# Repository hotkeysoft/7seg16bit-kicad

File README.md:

# Six-digit seven-segment indicator for 16 bit values
Rev A August 2019

- ATmega8535 microcontroller running at 8MHz (internal clock)
- 3x2 digit 7-segment display
- Configurable modes via jumpers:
  - Decimal / HEX mode
    - Signed Decimal (-32768-32767)
    - Unsigned Decimal (0-65535)
    - Hexadecimal (0-FFFF)
  - Latch mode
    - Latch value on L->H transition
    - Latch value on H->L transition
    - Unlatched (live display)

Images
============
|Front                                                 | Back                                              |
|------------------------------------------------------|---------------------------------------------------|
|||

### Schematics (pdf)
- [Complete schematics](./img/schema.pdf)

### PCB Images (svg)
- [Top](./img/pcb-front.svg)
- [Bottom](./img/pcb-back.svg)

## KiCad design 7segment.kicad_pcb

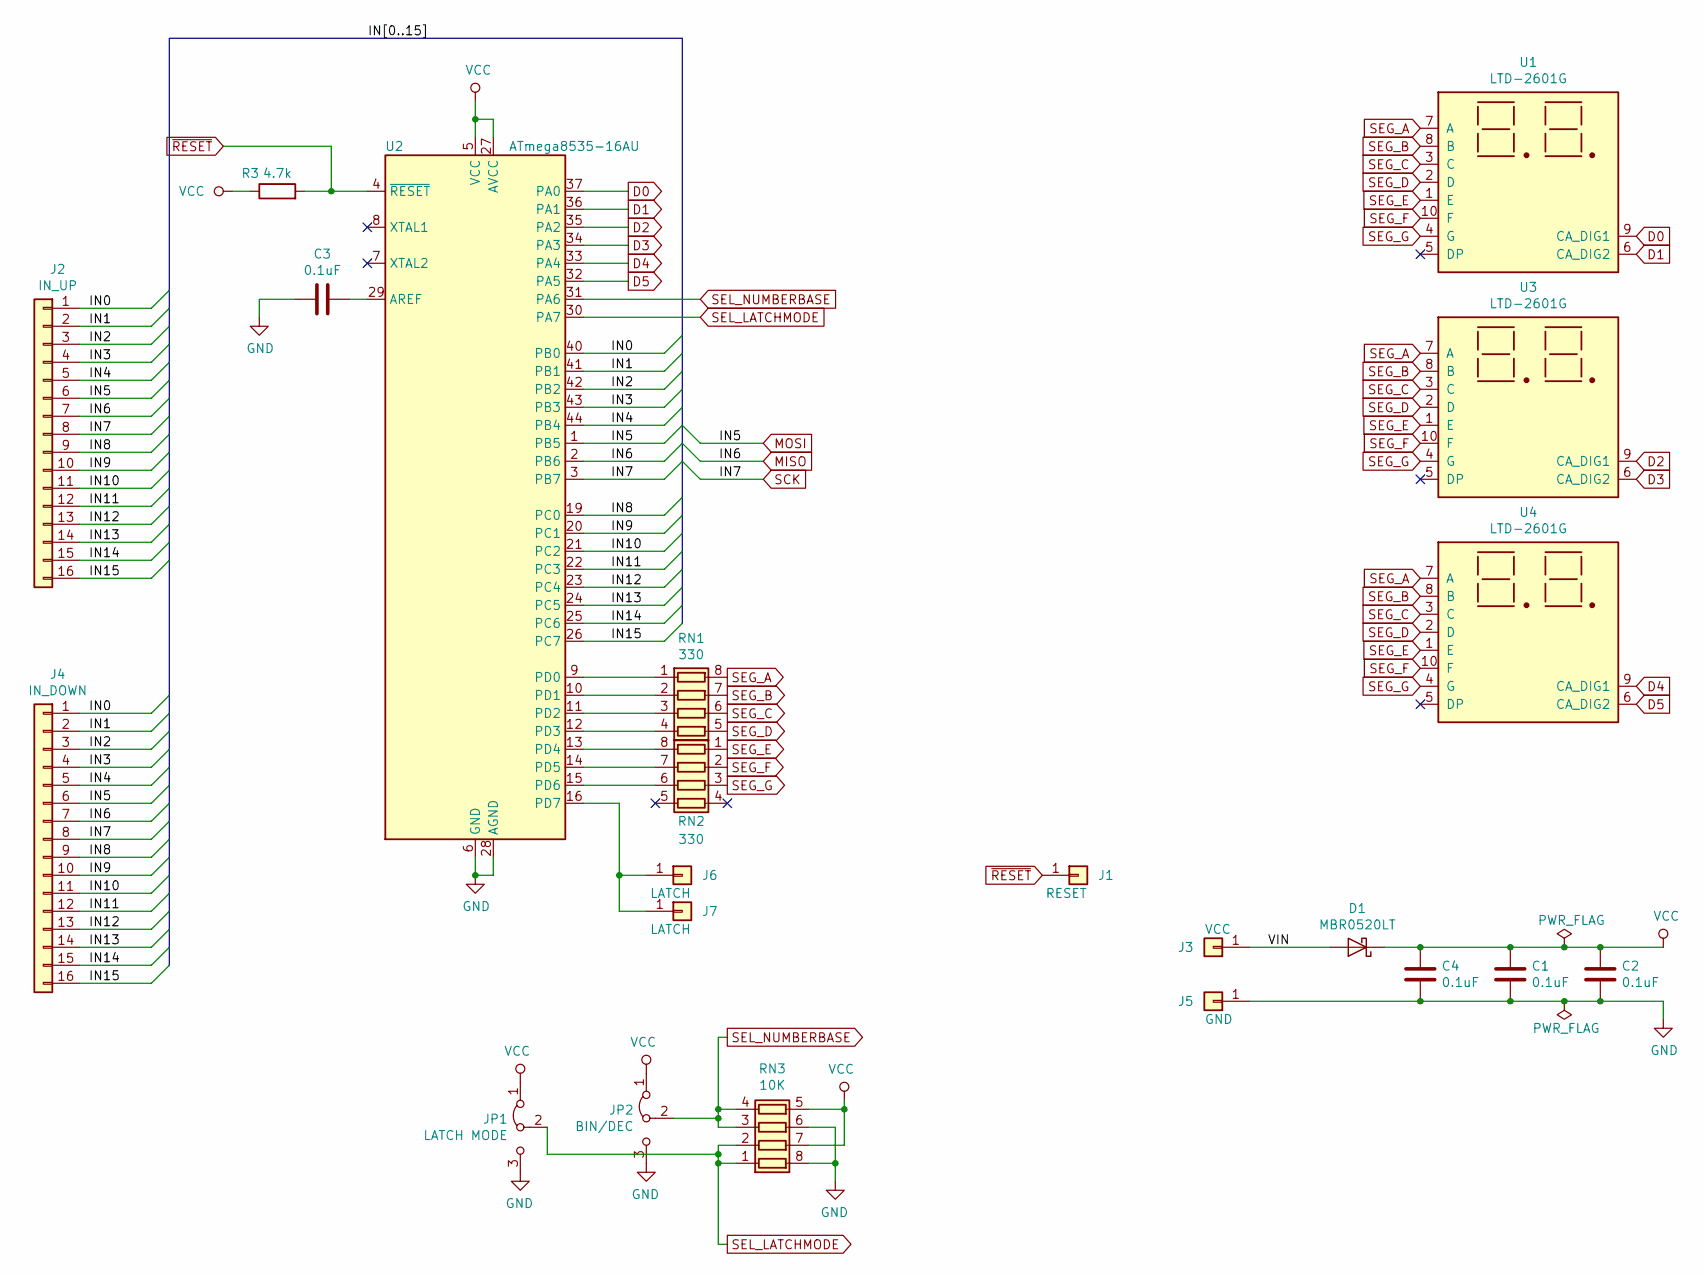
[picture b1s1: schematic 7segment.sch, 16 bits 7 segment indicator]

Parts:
C1, C2, C3, C4: 0.1uF; C_0805_2012Metric_Pad1.15x1.40mm_HandSolder
D1: MBR0520LT; D_SOD-123
J1: RESET; PinHeader_1x01_P2.54mm_Vertical
J2: IN_UP; PinHeader_1x16_P2.54mm_Vertical
J3: VCC; PinHeader_1x01_P2.54mm_Vertical
J4: IN_DOWN; PinHeader_1x16_P2.54mm_Vertical
J5: GND; PinHeader_1x01_P2.54mm_Vertical
J6, J7: LATCH; PinHeader_1x01_P2.54mm_Vertical
JP1: LATCH MODE; PinHeader_1x03_P2.54mm_Vertical
JP2: BIN/DEC; PinHeader_1x03_P2.54mm_Vertical
R3: 4.7k; R_0805_2012Metric_Pad1.15x1.40mm_HandSolder
RN1, RN2: 330; R_Array_Convex_4x0603
RN3: 10K; R_Array_Convex_4x0603
U1, U3, U4: LTD-2601G
U2: ATmega8535-16AU; TQFP-44_10x10mm_P0.8mm

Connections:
/IN0: J2.1, J4.1, U2.40 (PB0)
/IN1: J2.2, J4.2, U2.41 (PB1)
/IN2: J2.3, J4.3, U2.42 (PB2)
/IN3: J2.4, J4.4, U2.43 (PB3)
/IN4: J2.5, J4.5, U2.44 (PB4)
/IN8: J2.9, J4.9, U2.19 (PC0)
/IN9: J2.10, J4.10, U2.20 (PC1)
/IN10: J2.11, J4.11, U2.21 (PC2)
/IN11: J2.12, J4.12, U2.22 (PC3)
/IN12: J2.13, J4.13, U2.23 (PC4)
/IN13: J2.14, J4.14, U2.24 (PC5)
/IN14: J2.15, J4.15, U2.25 (PC6)
/IN15: J2.16, J4.16, U2.26 (PC7)
/VIN: D1.2 (A), J3.1
D0: U1.9 (CA_DIG1), U2.37 (PA0)
D1: U1.6 (CA_DIG2), U2.36 (PA1)
D2: U2.35 (PA2), U3.9 (CA_DIG1)
D3: U2.34 (PA3), U3.6 (CA_DIG2)
D4: U2.33 (PA4), U4.9 (CA_DIG1)
D5: U2.32 (PA5), U4.6 (CA_DIG2)
GND: C1.2, C2.2, C3.1, C4.2, J5.1, JP1.3 (B), JP2.3 (B), RN3.6 (R3.2), RN3.8 (R1.2), U2.6 (GND), U2.18 (GND), U2.28 (AGND), U2.39 (GND)
MISO: J2.7, J4.7, U2.2 (PB6)
MOSI: J2.6, J4.6, U2.1 (PB5)
unnamed: C3.2, U2.29 (AREF)
unnamed: J6.1, J7.1, U2.16 (PD7)
unnamed: RN1.1 (R1.1), U2.9 (PD0)
unnamed: RN1.2 (R2.1), U2.10 (PD1)
unnamed: RN1.3 (R3.1), U2.11 (PD2)
unnamed: RN1.4 (R4.1), U2.12 (PD3)
unnamed: RN2.6 (R3.2), U2.15 (PD6)
unnamed: RN2.7 (R2.2), U2.14 (PD5)
unnamed: RN2.8 (R1.2), U2.13 (PD4)
SCK: J2.8, J4.8, U2.3 (PB7)
SEG_A: RN1.8 (R1.2), U1.7 (A), U3.7 (A), U4.7 (A)
SEG_B: RN1.7 (R2.2), U1.8 (B), U3.8 (B), U4.8 (B)
SEG_C: RN1.6 (R3.2), U1.3 (C), U3.3 (C), U4.3 (C)
SEG_D: RN1.5 (R4.2), U1.2 (D), U3.2 (D), U4.2 (D)
SEG_E: RN2.1 (R1.1), U1.1 (E), U3.1 (E), U4.1 (E)
SEG_F: RN2.2 (R2.1), U1.10 (F), U3.10 (F), U4.10 (F)
SEG_G: RN2.3 (R3.1), U1.4 (G), U3.4 (G), U4.4 (G)
SEL_LATCHMODE: JP1.2 (C), RN3.1 (R1.1), RN3.2 (R2.1), U2.30 (PA7)
SEL_NUMBERBASE: JP2.2 (C), RN3.3 (R3.1), RN3.4 (R4.1), U2.31 (PA6)
VCC: C1.1, C2.1, C4.1, D1.1 (K), JP1.1 (A), JP2.1 (A), R3.1, RN3.5 (R4.2), RN3.7 (R2.2), U2.5 (VCC), U2.17 (VCC), U2.27 (AVCC), U2.38 (VCC)
~RESET: J1.1, R3.2, U2.4 (~RESET)

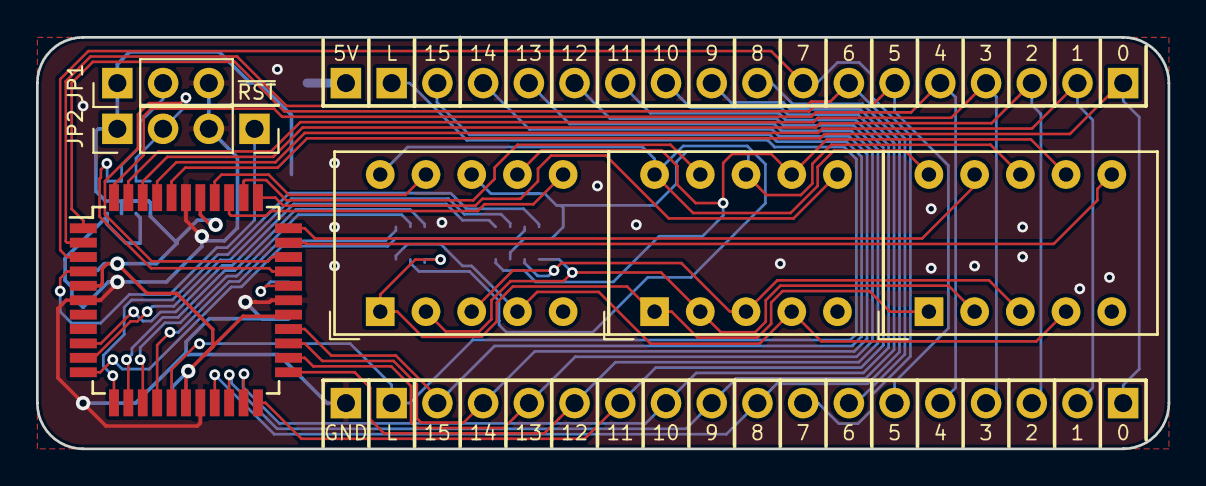
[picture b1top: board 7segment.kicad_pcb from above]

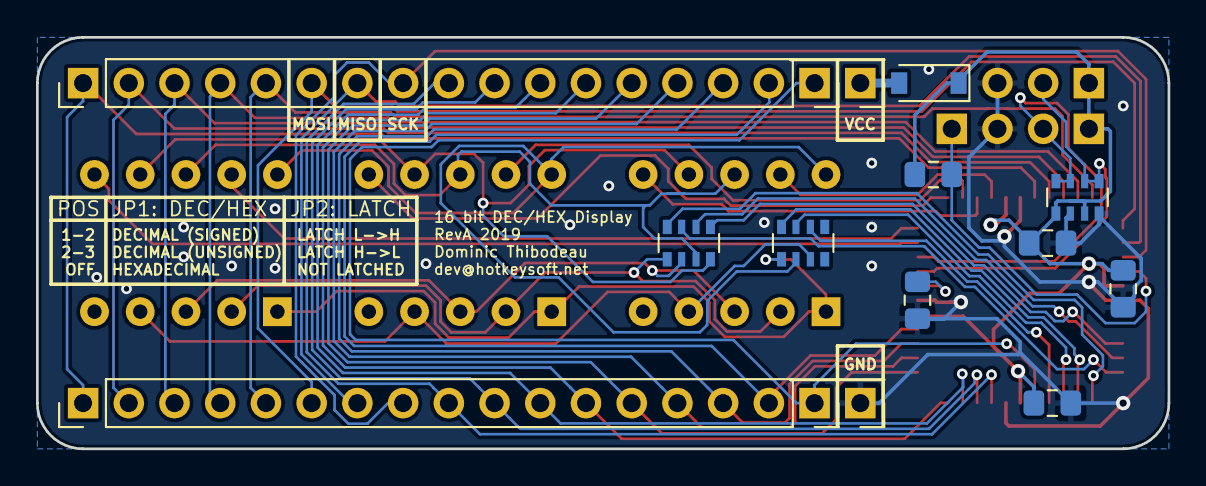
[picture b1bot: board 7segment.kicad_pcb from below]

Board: 2 copper layers, 62.9 x 22.9 mm, 22 parts (15 on the bottom side), 44 nets.

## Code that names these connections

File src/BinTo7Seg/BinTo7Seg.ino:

/* Binary to 7 Segment display (16 bits)
 * Rev A 
 * 2019-08-19 Dominic Thibodeau
 * 
 * Modes: Hex / Signed Decimal / Unsigned Decimal
 *        Latched / Live
 *        
 * Target: ATmega8535
 */

/*
 * IN0-IN7:  PB0-PB7
 * IN8-IN15: PC0-PC7
 * 
 * D0: PA0
 * D1: PA1
 * D2: PA2
 * D3: PA3
 * D4: PA4
 * D5: PA5
 * 
 * IN_LATCH: PD7
 * 
 * SEGA-SEGG: PD0-PD6
 * 
 * SEL_NUMBERBASE: PA6
 * SEL_LATCHMODE: PA7
 */

#define PA 0
#define PB 1
#define PC 2
#define PD 3

#define SEL_D0 24
#define SEL_D1 25
#define SEL_D2 26
#define SEL_D3 27
#define SEL_D4 28
#define SEL_D5 29

#define SEL_NUMBERBASE A6
#define SEL_LATCHMODE A7

#define IN_LATCH 15

const int digitDelay = 2;

bool triggeredOnce = false;
int lastLatchPinState;
uint16_t latchedInput = 0;

enum DIGIT {
  DIGIT_D0 = SEL_D0,
  DIGIT_D1 = SEL_D1,
  DIGIT_D2 = SEL_D2,
  DIGIT_D3 = SEL_D3,
  DIGIT_D4 = SEL_D4,
  DIGIT_D5 = SEL_D5,
};

enum LATCHMODE {
  LATCH_LH,
  LATCH_HL,
  LATCH_LIVE
};

enum NUMBERBASE {
  NB_SIGNED_DEC,
  NB_UNSIGNED_DEC,
  NB_HEX
};

LATCHMODE getLatchMode() {
  int value = analogRead(SEL_LATCHMODE);
  if (value < 300)
    return LATCH_LH;
  else if (value > 700)
    return LATCH_HL;
  else 
    return LATCH_LIVE;  
}

NUMBERBASE getNumberBase() {
  int value = analogRead(SEL_NUMBERBASE);
  if (value < 300)
    return NB_SIGNED_DEC;
  else if (value > 700)
    return NB_UNSIGNED_DEC;
  else 
    return NB_HEX;      
}

uint16_t readInput() {
  return (portRead(PC) << 8) + portRead(PB);
}

void setup() {
  // Segments
  portMode(PD, OUTPUT);
  
  // Inputs
  portMode(PB, INPUT);
  portMode(PC, INPUT);

  pinMode(SEL_D0, OUTPUT);
  pinMode(SEL_D1, OUTPUT);
  pinMode(SEL_D2, OUTPUT);
  pinMode(SEL_D3, OUTPUT);
  pinMode(SEL_D4, OUTPUT);
  pinMode(SEL_D5, OUTPUT);  

  pinMode(IN_LATCH, INPUT_PULLUP); //TODODT: remove pullup in prod  
  lastLatchPinState = digitalRead(IN_LATCH);
}

const PROGMEM byte digits[17] = {
  0b00111111, // 0
  0b00000110, // 1
  0b01011011, // 2  
  0b01001111, // 3
  0b01100110, // 4
  0b01101101, // 5
  0b01111101, // 6
  0b00000111, // 7 
  0b01111111, // 8
  0b01101111, // 9 
  0b01110111, // A
  0b01111100, // b
  0b00111001, // C
  0b01011110, // d
  0b01111001, // E
  0b01110001, // F
  0b01000000  // -
};

void outputBlank(DIGIT pos) {
  clearDigits();
  portWrite(PD, 255);
  selectDigit(pos);
}

void outputMinus(DIGIT pos) {
  clearDigits();
  portWrite(PD, ~pgm_read_byte_near(digits + 16));
  selectDigit(pos);  
}

void outputDigit(const byte digit, DIGIT pos) {
  clearDigits();
  if (digit > 15) return;
  portWrite(PD, ~pgm_read_byte_near(digits + digit));
  selectDigit(pos);  
}

void clearDigits() {
  digitalWrite(SEL_D0, LOW);
  digitalWrite(SEL_D1, LOW);
  digitalWrite(SEL_D2, LOW);
  digitalWrite(SEL_D3, LOW);
  digitalWrite(SEL_D4, LOW);
  digitalWrite(SEL_D5, LOW);  
}

void selectDigit(DIGIT digit) {
  digitalWrite(digit, HIGH);
}

void outputNumberHex(const uint16_t number) {
  outputBlank(DIGIT_D0);
  delay(digitDelay);

  outputBlank(DIGIT_D1);
  delay(digitDelay);
 
  outputDigit(number >> 12, DIGIT_D2);
  delay(digitDelay);

  outputDigit((number >> 8) & 0x0F, DIGIT_D3);
  delay(digitDelay);
  
  outputDigit((number >> 4) & 0x0F, DIGIT_D4);
  delay(digitDelay);

  outputDigit(number&0x0F, DIGIT_D5);
  delay(digitDelay);
}

void outputNumberUnsignedDecimal(uint16_t number) {
  if (number > 9999) {
    outputDigit(number/10000, DIGIT_D1);
  }
  else {
    outputBlank(DIGIT_D1);
  }
  delay(digitDelay);  
  
  if (number > 999) {
    outputDigit((number/1000)%10, DIGIT_D2);
  } else {
    outputBlank(DIGIT_D2);    
  }
  delay(digitDelay);      
  
  if (number > 99) {
    outputDigit((number/100)%10, DIGIT_D3);
  } else {
    outputBlank(DIGIT_D3);    
  }
  delay(digitDelay);    
  
  if (number > 9) {
    outputDigit((number/10)%10, DIGIT_D4);
  } else {
    outputBlank(DIGIT_D4);
  }
  delay(digitDelay);

  outputDigit(number%10, DIGIT_D5);
  delay(digitDelay);
}

void outputNumberSignedDecimal(uint16_t number) {
  if (number > 32767) {
    uint16_t unsignedValue = -number;

    outputNumberUnsignedDecimal(unsignedValue);  

    if (unsignedValue > 9999)
      outputMinus(DIGIT_D0);
    else if (unsignedValue > 999)
      outputMinus(DIGIT_D1);
    else if (unsignedValue > 99)
      outputMinus(DIGIT_D2);
    else if (unsignedValue > 9)
      outputMinus(DIGIT_D3);
    else 
      outputMinus(DIGIT_D4);

    delay(digitDelay);      
  } else {
    outputNumberUnsignedDecimal(number);
  }
}

void outputNumber(uint16_t number) {
  switch(getNumberBase()) {
    case NB_SIGNED_DEC:
      outputNumberSignedDecimal(number);
      break;
    case NB_UNSIGNED_DEC:
      outputNumberUnsignedDecimal(number);
      break;
    default:
      outputNumberHex(number);
  }
}

void loop() { 
  clearDigits();
  
  LATCHMODE latchMode = getLatchMode();

  if (latchMode != LATCH_LIVE) {
    bool triggered = false;
    int currLatchState = digitalRead(IN_LATCH);
    triggered = ((latchMode == LATCH_LH) && !lastLatchPinState && currLatchState) || 
      ((latchMode == LATCH_HL) && lastLatchPinState && !currLatchState);
    lastLatchPinState = currLatchState;

    if (triggered) {
      triggeredOnce = true;
      latchedInput = readInput();;
    }
    if (triggeredOnce) {
      outputNumber(latchedInput);
    }
  } else {   
    outputNumber(readInput());
  }
}

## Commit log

2019-08-21 Routing
2019-08-23 Add PCB Fabrication zip files
2019-08-28 16 bit version
2019-09-05 Fixed negative number issue. Improved uneven brightness and ghost segments
2019-10-21 update kicad
2020-07-28 Cleanup, added commonlib
2020-07-28 Added images
2020-07-28 Create LICENSE
2020-07-28 Added commonlib submodule
